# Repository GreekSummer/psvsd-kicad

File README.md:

# PSVSD KiCad source

This is a fork of [Yinfanlu's PSVSD adapter](https://github.com/yifanlu/psvsd/). Its main purpose is to adapt the original Eagle Autodesk files to KiCad, which is open source and free. 

The conversion was done using KiCad's own importer. The result was mostly complete with various issues that had to be manually corrected. The result has not yet been produced, so assume there are still issues.

I removed the debug headers to simplify the board. Most people do not need these. I also replaced the SD slot with one that is easier to find and source.

A big problem with these is sourcing the main USB-to-SD IC. As of August 15th 2025, I was able to find the GL823A-QFN24 on AliExpress for $3.30 per IC. The rest of the parts cost ~$5.03 on DigiKey.

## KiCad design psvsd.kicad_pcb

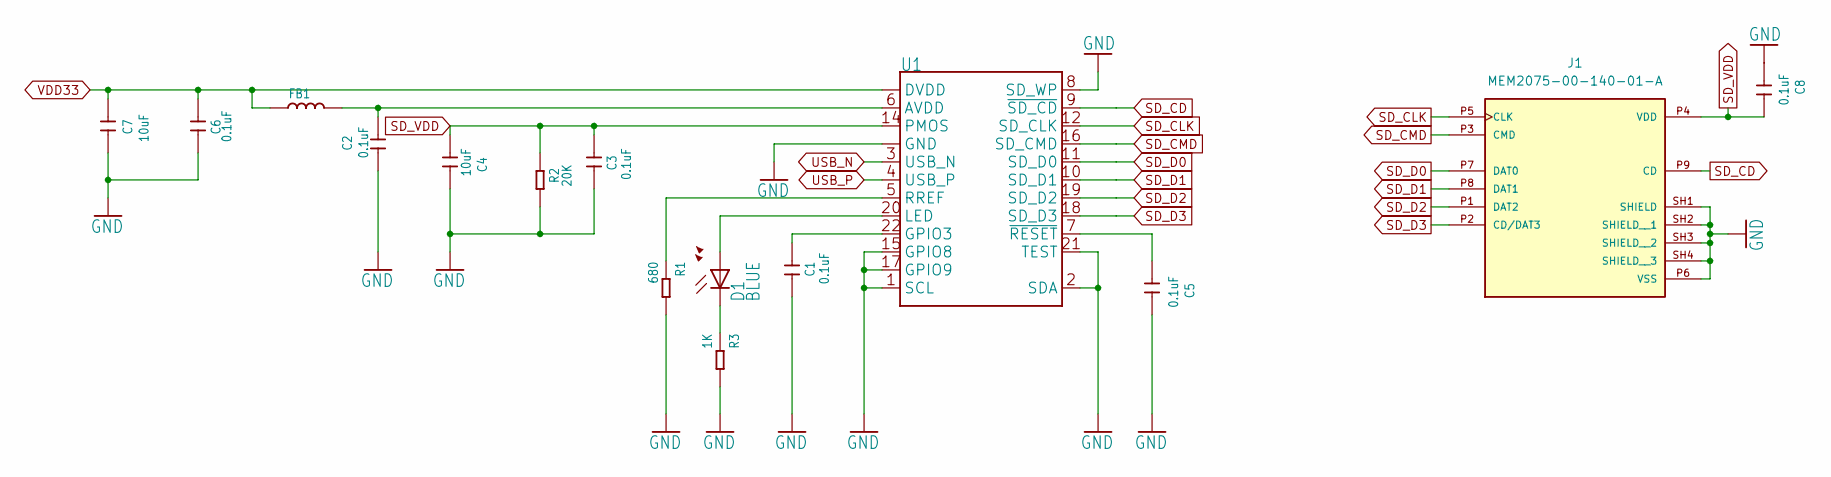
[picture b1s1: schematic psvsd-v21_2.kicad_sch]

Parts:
C1, C2, C3, C5, C6, C8: 0.1uF; C0603_464
C4, C7: 10uF; C0603_464
D1: BLUE; CHIP-LED0603_259
FB1: SMD-FERRITE-BEAD-2500R-50MA(0603); L0603_471
J1: MEM2075-00-140-01-A; GCT_MEM2075-00-140-01-A; PARTREV A
R1: 680; R0603_474
R2: 20K; R0603_474
R3: 1K; R0603_474
U1: GL823(A)OG; QFN-24

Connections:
GND: C1.2, C2.2, C3.2, C4.2, C5.2, C6.2, C7.2, C8.2, J1.P6 (VSS), J1.SH1 (SHIELD), J1.SH2 (SHIELD__1), J1.SH3 (SHIELD__2), J1.SH4 (SHIELD__3), R1.2, R2.2, R3.2, U1.1 (SCL), U1.2 (SDA), U1.8 (SD_WP), U1.15 (GPIO8), U1.17 (GPIO9), U1.21 (TEST), U1.24 (GND), U1.25 (GND); also elsewhere on the board
unnamed: D1.C, R3.1
unnamed: C2.1, FB1.2, U1.6 (AVDD)
unnamed: C1.1, U1.22 (GPIO3)
unnamed: D1.A, U1.20 (LED)
unnamed: R1.1, U1.5 (RREF)
unnamed: C5.1, U1.7 (~RESET)
SD_CD: J1.P9 (CD), U1.9 (~SD_CD)
SD_CLK: J1.P5 (CLK), U1.12 (SD_CLK)
SD_CMD: J1.P3 (CMD), U1.16 (SD_CMD)
SD_D0: J1.P7 (DAT0), U1.11 (SD_D0)
SD_D1: J1.P8 (DAT1), U1.10 (SD_D1)
SD_D2: J1.P1 (DAT2), U1.19 (SD_D2)
SD_D3: J1.P2 (CD/DAT3), U1.18 (SD_D3)
SD_VDD: C3.1, C4.1, C8.1, J1.P4 (VDD), R2.1, U1.14 (PMOS)
USB_N: U1.3 (USB_N); also elsewhere on the board
USB_P: U1.4 (USB_P); also elsewhere on the board
VDD33: C6.1, C7.1, FB1.1, U1.13 (DVDD), U1.23 (DVDD); also elsewhere on the board

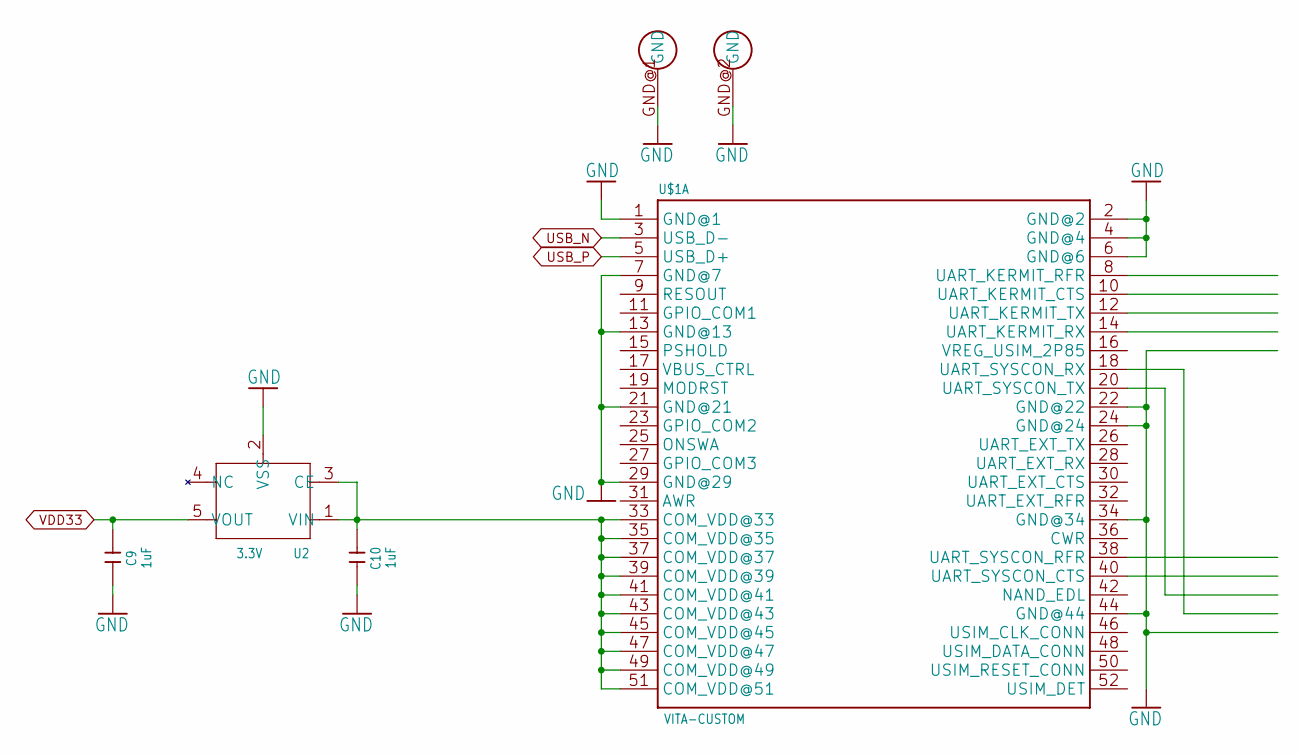
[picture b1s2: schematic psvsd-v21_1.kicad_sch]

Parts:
C9, C10: 1uF; C0603_464
U2: 3.3V; SOT-23-5_470
U$1: VITA-CUSTOM; VITA-MINI-PCI-E

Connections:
GND: C9.2, C10.2, U2.2 (VSS), U$1.1 (GND@1), U$1.2 (GND@2), U$1.4 (GND@4), U$1.6 (GND@6), U$1.7 (GND@7), U$1.13 (GND@13), U$1.21 (GND@21), U$1.22 (GND@22), U$1.24 (GND@24), U$1.29 (GND@29), U$1.34 (GND@34), U$1.44 (GND@44), U$1.GND@1 (GND), U$1.GND@2 (GND); also elsewhere on the board
unnamed: C10.1, U2.1 (VIN), U2.3 (CE), U$1.33 (COM_VDD@33), U$1.35 (COM_VDD@35), U$1.37 (COM_VDD@37), U$1.39 (COM_VDD@39), U$1.41 (COM_VDD@41), U$1.43 (COM_VDD@43), U$1.45 (COM_VDD@45), U$1.47 (COM_VDD@47), U$1.49 (COM_VDD@49), U$1.51 (COM_VDD@51)
USB_N: U$1.3 (USB_D-); also elsewhere on the board
USB_P: U$1.5 (USB_D+); also elsewhere on the board
VDD33: C9.1, U2.5 (VOUT); also elsewhere on the board

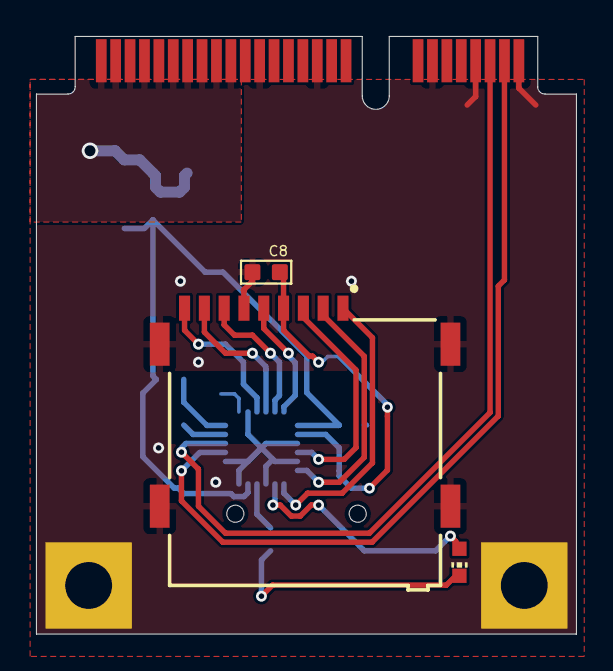
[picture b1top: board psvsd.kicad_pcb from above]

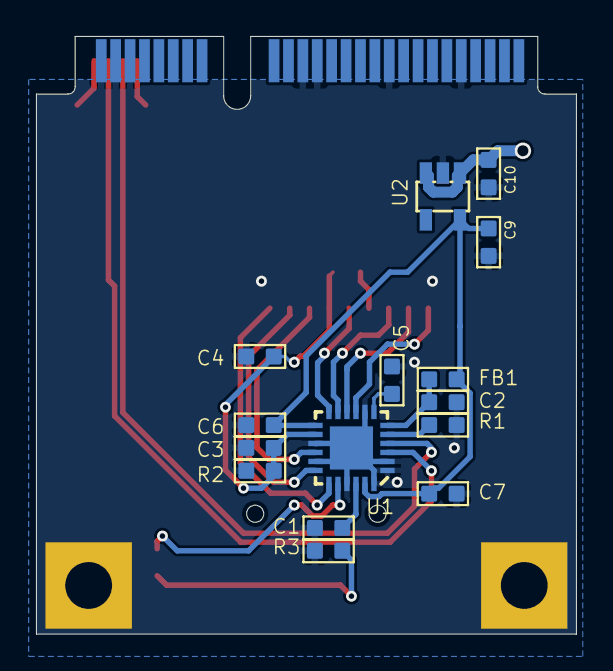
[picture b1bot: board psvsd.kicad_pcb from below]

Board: 2 copper layers, 30.0 x 33.2 mm, 19 parts (15 on the bottom side), 19 nets.

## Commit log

2025-08-14 Update files to KiCad
2025-09-26 Update README.md
    minor grammar correction
